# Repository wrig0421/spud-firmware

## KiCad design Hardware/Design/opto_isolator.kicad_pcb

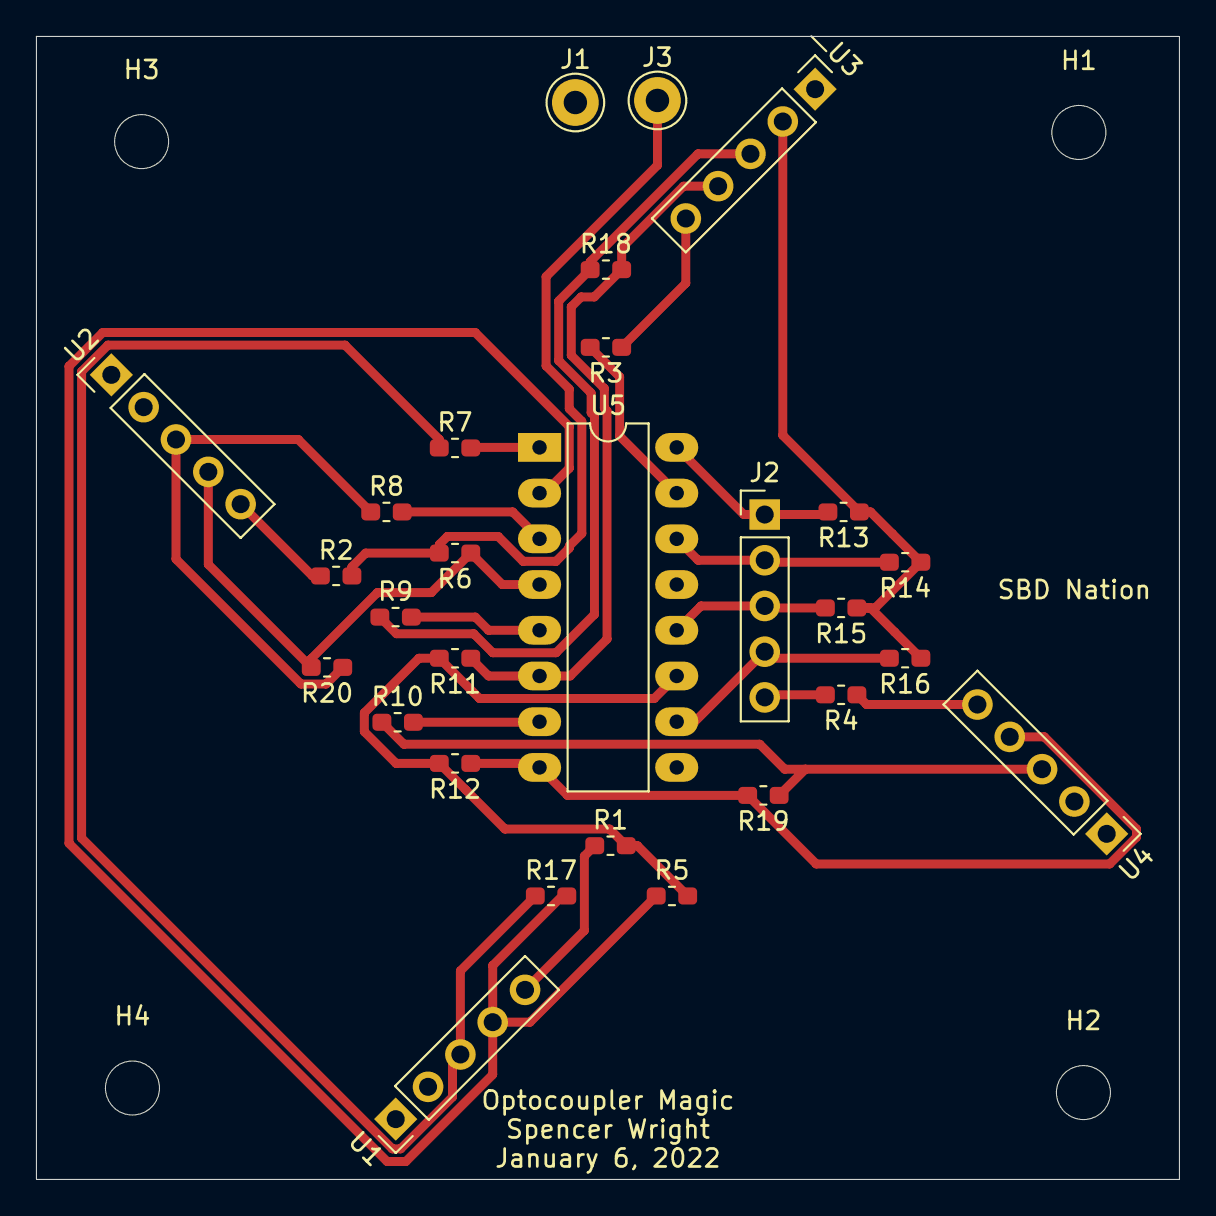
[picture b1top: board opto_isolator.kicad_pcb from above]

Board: 4 copper layers, 63.5 x 63.5 mm, 32 parts (0 on the bottom side), 22 nets.

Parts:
H1, H2, H3, H4: MountingHole; MountingHole_3mm
J1, J3: Conn_01x01_Male; Pin_D1.3mm_L11.0mm
J2: Conn_01x05_Male; PinHeader_1x05_P2.54mm_Vertical
R1, R2, R3, R4, R5, R6, R11, R12, R17, R18, R19, R20: DNI; R_0603_1608Metric_Pad1.05x0.95mm_HandSolder
R7, R8, R9, R10: 1k; R_0603_1608Metric_Pad1.05x0.95mm_HandSolder
R13, R14, R15, R16: 10k; R_0603_1608Metric_Pad1.05x0.95mm_HandSolder
U1, U2, U3, U4: receiver_433MHz; PinHeader_1x05_P2.54mm_Vertical
U5: PS2501-4; DIP-16_W7.62mm_LongPads

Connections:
/INT_0: J2.1, R13.2, U5.16
/INT_1: J2.2, R14.2, U5.14
/INT_2: J2.3, R15.2, U5.12
/INT_3: J2.4, R16.2, U5.10
/OUT_1_N: R5.1, R17.2, U1.4, U5.2
/OUT_1_P: R7.1, R17.1, U1.3
/OUT_2_N: R6.1, R20.2, U2.4, U5.4
/OUT_2_P: R8.1, R20.1, U2.3
/OUT_3_N: R11.1, R18.2, U3.4, U5.6
/OUT_3_P: R9.1, R18.1, U3.3
/OUT_4_N: R12.1, R19.2, U4.4, U5.8
/OUT_4_P: R10.1, R19.1, U4.3
GND: J2.5, J3.1, R1.2, R2.2, R3.2, R4.2, R5.2, R6.2, R11.2, R12.2, U1.1, U2.1, U3.1, U4.1, U5.9, U5.11, U5.13, U5.15
unnamed: R1.1, U1.5
unnamed: R2.1, U2.5
unnamed: R3.1, U3.5
unnamed: R4.1, U4.5
unnamed: R7.2, U5.1
unnamed: R8.2, U5.3
unnamed: R9.2, U5.5
unnamed: R10.2, U5.7
VCC: J1.1, R13.1, R14.1, R15.1, R16.1, U1.2, U2.2, U3.2, U4.2

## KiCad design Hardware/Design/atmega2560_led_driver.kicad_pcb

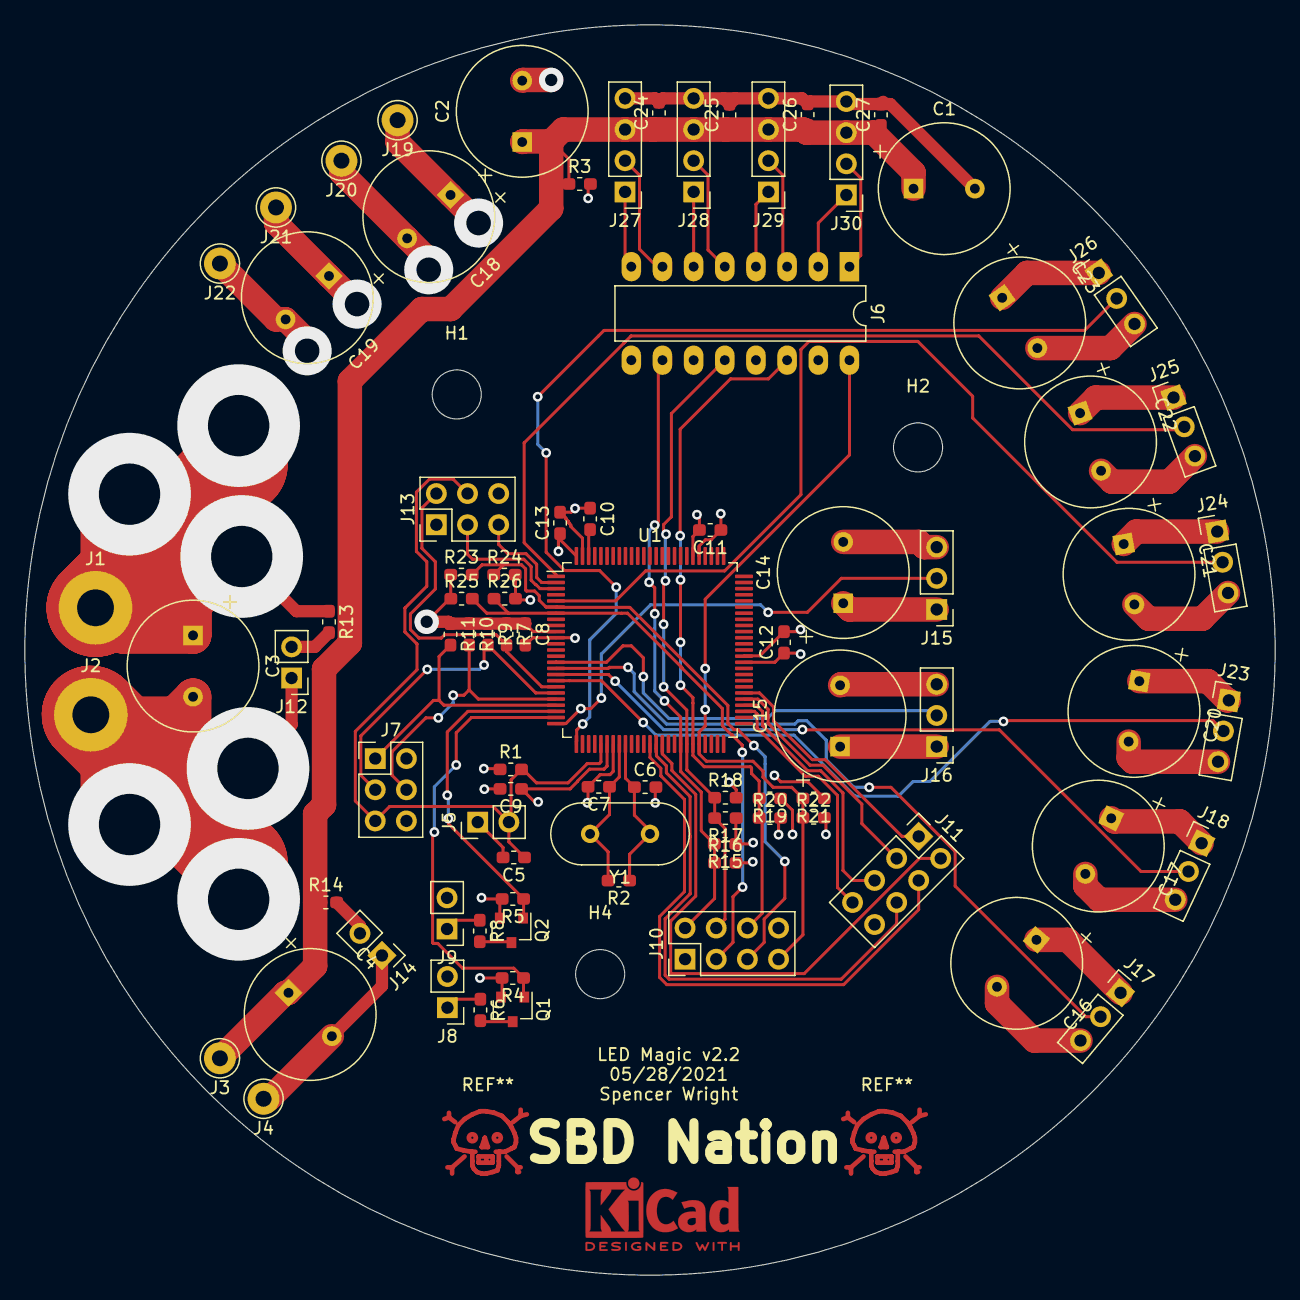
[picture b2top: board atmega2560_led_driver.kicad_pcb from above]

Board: 4 copper layers, 101.9 x 101.9 mm, 89 parts (0 on the bottom side), 50 nets.

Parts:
C1, C2, C3, C4, C14, C15, C16, C17, C18, C19, C20, C21, C22, C23: 10u; CP_Radial_Tantal_D10.5mm_P5.00mm
C5, C24, C25, C26, C27: 1u; R_0603_1608Metric_Pad1.05x0.95mm_HandSolder
C6, C7: CP1_Small; C_0603_1608Metric_Pad1.05x0.95mm_HandSolder
C8, C9, C10: 0.1u; R_0603_1608Metric_Pad1.05x0.95mm_HandSolder
C11, C12, C13: 0.1u; C_0603_1608Metric_Pad1.05x0.95mm_HandSolder
H1, H2, H4: MountingHole; MountingHole_4mm
J1, J2: Conn_01x01_Male; MountingHole_3mm_Pad
J3, J4, J19, J20, J21, J22: Conn_01x01_Male; Pin_D1.3mm_L11.0mm
J5, J8, J9, J12, J14: Conn_01x02_Male; PinHeader_1x02_P2.54mm_Vertical
J6: Conn_02x08_Counter_Clockwise; DIP-16_W7.62mm_LongPads
J7, J13: Conn_02x03_Odd_Even; PinHeader_2x03_P2.54mm_Vertical
J10, J11: Conn_02x04_Odd_Even; PinHeader_2x04_P2.54mm_Vertical
J15, J16, J17, J18, J23, J24, J25, J26: Conn_01x03_Male; PinHeader_1x03_P2.54mm_Vertical
J27, J28, J29, J30: Conn_01x04_Male; PinHeader_1x04_P2.54mm_Vertical
Q1, Q2: BSS138; SOT-23
R1, R7, R9, R10, R11, R15, R17, R19, R21, R23, R25: 10k; R_0603_1608Metric_Pad1.05x0.95mm_HandSolder
R2, R3, R4, R5: 1M; R_0603_1608Metric_Pad1.05x0.95mm_HandSolder
R6, R8: 100; R_0603_1608Metric_Pad1.05x0.95mm_HandSolder
R13: 1k; R_0603_1608Metric_Pad1.05x0.95mm_HandSolder
R14: 2.2k; R_0603_1608Metric_Pad1.05x0.95mm_HandSolder
R16, R18, R20, R22, R24, R26: DNI; R_0603_1608Metric_Pad1.05x0.95mm_HandSolder
U1: ATmega2560-16AU; TQFP-100_14x14mm_P0.5mm
Y1: 8M; Crystal_HC49-U_Vertical

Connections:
+5V: C3.1, C8.1, C9.1, C11.1, C12.1, C13.1, C14.1, C15.1, C16.1, C17.1, C18.1, C19.1, C20.1, C21.1, C22.1, C23.1, J1.1, J7.2, J8.2, J9.2, J10.1, J13.1, J15.1, J16.1, J17.1, J18.1, J19.1, J21.1, J23.1, J24.1, J25.1, J26.1, R1.1, R7.1, R9.1, R10.1, R11.1, R13.1, R15.1, R17.1, R19.1, R21.1, R23.1, R25.1, U1.10, U1.31, U1.61, U1.80, U1.100
+9V: C1.1, C2.1, C4.1, C24.1, C25.1, C26.1, C27.1, J3.1, J27.3, J28.3, J29.3, J30.3, R3.1, R14.1
/ATMEGA_D0_RX0: J13.5, U1.2
/ATMEGA_D1_TX0: J13.3, U1.3
/ATMEGA_D2_INT4: J10.5, R23.2, R24.1, U1.6
/ATMEGA_D3_INT5: J10.3, R25.2, R26.1, U1.7
/ATMEGA_D4_LED_OUT_7: J25.2, U1.1
/ATMEGA_D5_LED_OUT_6: J24.2, U1.5
/ATMEGA_D6_LED_OUT_2: J16.2, U1.15
/ATMEGA_D7_LED_OUT_3: J17.2, U1.16
/ATMEGA_D8_LED_OUT_4: J18.2, U1.17
/ATMEGA_D9_LED_OUT_5: J23.2, U1.18
/ATMEGA_D10_RED_LED: Q2.1, R5.1, U1.23
/ATMEGA_D11_GRN_LED: Q1.1, R4.1, U1.24
/ATMEGA_D12_LED_OUT_1: J15.2, U1.25
/ATMEGA_D13_LED_OUT_8: J26.2, U1.26
/ATMEGA_D18_INT3: J6.16, J10.7, R21.2, R22.1, U1.46
/ATMEGA_D19_INT2: J6.14, J10.6, R19.2, R20.1, U1.45
/ATMEGA_D20_INT1: J6.12, J10.4, R17.2, R18.1, U1.44
/ATMEGA_D21_INT0: J6.10, J10.2, R15.2, R16.1, U1.43
/ATMEGA_D34_GPIO: J11.1, U1.56
/ATMEGA_D35_GPIO: J11.3, U1.55
/ATMEGA_D36_GPIO: J11.5, U1.54
/ATMEGA_D37_GPIO: J11.7, U1.53
/ATMEGA_D44_GPIO: J11.2, U1.40
/ATMEGA_D45_GPIO: J11.6, U1.39
/ATMEGA_D46_GPIO: J11.4, U1.38
/ATMEGA_MISO: J7.1, R11.2, U1.22
/ATMEGA_MOSI: J7.4, R10.2, U1.21
/ATMEGA_NSS: J13.2, R7.2, U1.19
/ATMEGA_SCK: J7.3, R9.2, U1.20
/NRST: C5.1, J5.2, J7.5, J13.4, R1.2, U1.30
/OPTO_INT0_N: J6.8, J27.1
/OPTO_INT0_P: J6.7, J27.2
/OPTO_INT1_N: J6.6, J28.1
/OPTO_INT1_P: J6.5, J28.2
/OPTO_INT2_N: J6.4, J29.1
/OPTO_INT2_P: J6.3, J29.2
/OPTO_INT3_N: J6.2, J30.1
/OPTO_INT3_P: J6.1, J30.2
/XTAL1_HI: C6.1, R2.1, U1.34, Y1.1
/XTAL2_HI: C7.1, R2.2, U1.33, Y1.2
GND: C1.2, C2.2, C3.2, C4.2, C5.2, C6.2, C7.2, C8.2, C9.2, C10.1, C11.2, C12.2, C13.2, C14.2, C15.2, C16.2, C17.2, C18.2, C19.2, C20.2, C21.2, C22.2, C23.2, C24.2, C25.2, C26.2, C27.2, J2.1, J4.1, J5.1, J6.9, J6.11, J6.13, J6.15, J7.6, J10.8, J11.8, J12.1, J13.6, J14.1, J15.3, J16.3, J17.3, J18.3, J20.1, J22.1, J23.3, J24.3, J25.3, J26.3, J27.4, J28.4, J29.4, J30.4, Q1.2, Q2.2, R3.2, R4.2, R5.2, R16.2, R18.2, R20.2, R22.2, R24.2, R26.2, U1.11, U1.32, U1.62, U1.81, U1.99
unnamed: C10.2, U1.98
unnamed: J8.1, R6.1
unnamed: J9.1, R8.1
unnamed: J12.2, R13.2
unnamed: J14.2, R14.2
unnamed: Q1.3, R6.2
unnamed: Q2.3, R8.2

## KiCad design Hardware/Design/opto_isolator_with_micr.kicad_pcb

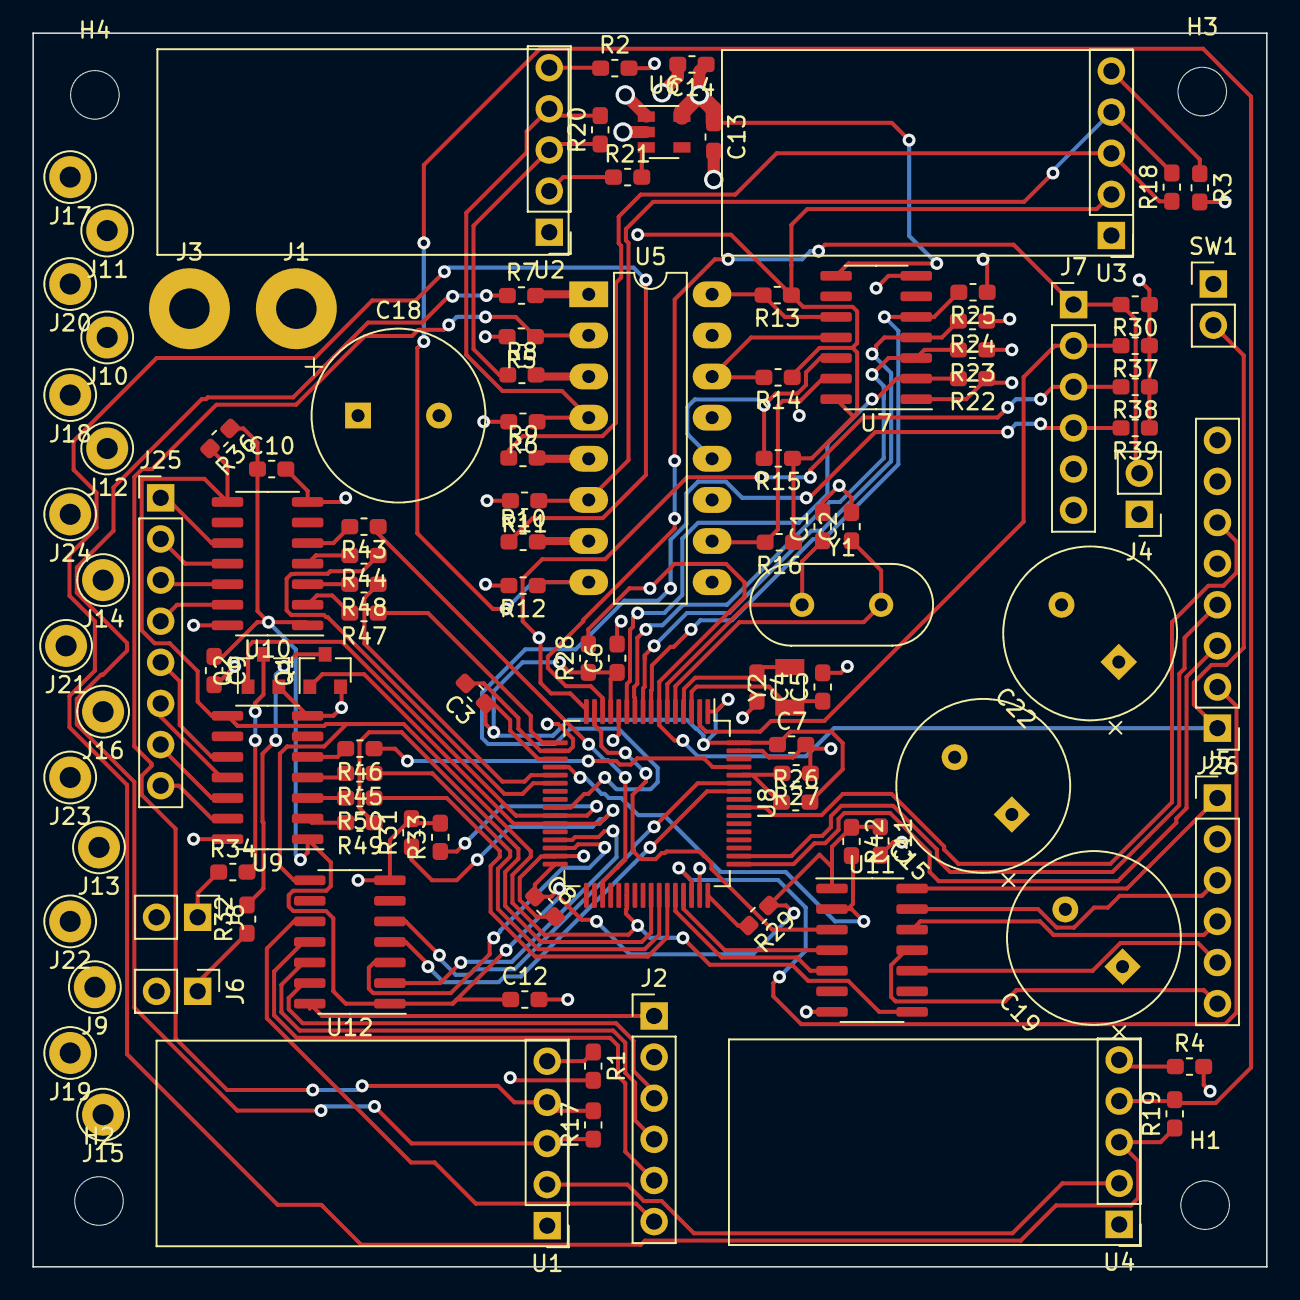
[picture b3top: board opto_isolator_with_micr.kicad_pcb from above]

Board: 4 copper layers, 76.2 x 76.2 mm, 112 parts (0 on the bottom side), 92 nets.

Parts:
C1, C2, C4, C5: CP1_Small; C_0603_1608Metric_Pad1.05x0.95mm_HandSolder
C3, C9, C10, C11, C12, C13: 1u; C_0603_1608Metric_Pad1.05x0.95mm_HandSolder
C6: 0.1u; C_0603_1608Metric_Pad1.05x0.95mm_HandSolder
C7: 0.01u; C_0603_1608Metric_Pad1.05x0.95mm_HandSolder
C8, C14: 10u; C_0603_1608Metric_Pad1.05x0.95mm_HandSolder
C15, C18, C19, C22: DNI; CP_Radial_Tantal_D10.5mm_P5.00mm
H1, H2, H3, H4: MountingHole; MountingHole_3mm
J1, J3: Conn_01x01_Male; MountingHole_2.5mm_Pad
J2, J5, J7: Conn_01x06_Male; PinHeader_1x06_P2.54mm_Vertical
J4, J6, J8: Conn_01x02_Male; PinHeader_1x02_P2.54mm_Vertical
J9, J10, J11, J12, J13, J14, J15, J16, J17, J18, J19, J20, J21, J22, J23, J24: Conn_01x01_Male; Pin_D1.3mm_L11.0mm
J25, J26: Conn_01x08_Male; PinHeader_1x08_P2.54mm_Vertical
Q1, Q2: BSS138; SOT-23
R1, R2, R3, R4, R5, R6, R11, R12, R18, R22, R23, R24, R25, R26: DNI; R_0603_1608Metric_Pad1.05x0.95mm_HandSolder
R7, R8, R9, R10, R30, R32, R34, R43, R44, R45, R46, R47, R48, R49, R50: 1k; R_0603_1608Metric_Pad1.05x0.95mm_HandSolder
R13, R14, R15, R16, R17, R19, R20, R21, R27, R37, R38, R39: 10k; R_0603_1608Metric_Pad1.05x0.95mm_HandSolder
R28, R31, R33, R36, R42: 100k; R_0603_1608Metric_Pad1.05x0.95mm_HandSolder
R29: 0; R_0603_1608Metric_Pad1.05x0.95mm_HandSolder
SW1: SW_Push; PinHeader_1x02_P2.54mm_Vertical
U1, U2, U3, U4: receiver_433MHz; PinHeader_1x05_P2.54mm_Vertical
U5: PS2501-4; DIP-16_W7.62mm_LongPads
U6: LD39015M18R; SOT-23-5
U7, U9, U10, U11, U12: TXB0104D; SOIC-14_3.9x8.7mm_P1.27mm
U8: STM32L431RCTx; LQFP-64_10x10mm_P0.5mm
Y1: Crystal; Crystal_HC49-U_Vertical
Y2: Crystal; Crystal_SMD_3215-2Pin_3.2x1.5mm

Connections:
+1V8: C3.1, C6.1, C7.1, C8.1, C9.1, C10.1, C11.1, C12.1, C13.1, C14.1, J7.5, J26.7, R22.1, R23.1, R24.1, R25.1, R26.2, R28.1, R29.1, R30.1, R36.1, R37.1, R38.1, R39.1, R42.1, U6.5, U7.1, U7.8, U8.1, U8.13, U8.19, U8.32, U8.64, U9.1, U10.1, U11.1, U12.1
+5V: C15.1, C18.1, C19.1, C22.1, J1.1, J6.2, J8.2, J9.1, J10.1, J11.1, J12.1, J13.1, J14.1, J15.1, J16.1, R13.1, R14.1, R15.1, R16.1, R21.1, U1.2, U2.2, U3.2, U4.2, U6.1, U7.14, U9.14, U10.14
/INT_0: R13.2, U5.16, U7.10
/INT_1: R14.2, U5.14, U7.11
/INT_2: R15.2, U5.12, U7.12
/INT_3: R16.2, U5.10, U7.13
/OUT_1_N: R5.1, R17.2, U1.4, U5.2
/OUT_1_P: R7.1, R17.1, U1.3
/OUT_2_N: R6.1, R20.2, U2.4, U5.4
/OUT_2_P: R8.1, R20.1, U2.3
/OUT_3_N: R11.1, R18.2, U3.4, U5.6
/OUT_3_P: R9.1, R18.1, U3.3
/OUT_4_N: R12.1, R19.2, U4.4, U5.8
/OUT_4_P: R10.1, R19.1, U4.3
/Sheet6227BA78/I2C2_SCL: U8.29, U12.2
/Sheet6227BA78/I2C2_SCL_SHIFTED: J2.3, U12.13
/Sheet6227BA78/I2C2_SDA: U8.30, U12.3
/Sheet6227BA78/I2C2_SDA_SHIFTED: J2.4, U12.12
/Sheet6227BA78/I2C_UART_VREF: J2.1, U12.14
/Sheet6227BA78/LED_GREEN: Q1.1, R31.1, U8.27
/Sheet6227BA78/LED_RED: Q2.1, R33.1, U8.26
/Sheet6227BA78/LED_STRIP_OUT_1: R47.2, U10.2
/Sheet6227BA78/LED_STRIP_OUT_1_SHIFTED: J25.4, U10.13
/Sheet6227BA78/LED_STRIP_OUT_2: R48.2, U10.3
/Sheet6227BA78/LED_STRIP_OUT_2_SHIFTED: J25.3, U10.12
/Sheet6227BA78/LED_STRIP_OUT_3: R44.2, U10.4
/Sheet6227BA78/LED_STRIP_OUT_3_SHIFTED: J25.2, U10.11
/Sheet6227BA78/LED_STRIP_OUT_4: R43.2, U10.5
/Sheet6227BA78/LED_STRIP_OUT_4_SHIFTED: J25.1, U10.10
/Sheet6227BA78/LED_STRIP_OUT_5: R49.2, U9.2
/Sheet6227BA78/LED_STRIP_OUT_5_SHIFTED: J25.8, U9.13
/Sheet6227BA78/LED_STRIP_OUT_6: R50.2, U9.3
/Sheet6227BA78/LED_STRIP_OUT_6_SHIFTED: J25.7, U9.12
/Sheet6227BA78/LED_STRIP_OUT_7: R45.2, U9.4
/Sheet6227BA78/LED_STRIP_OUT_7_SHIFTED: J25.6, U9.11
/Sheet6227BA78/LED_STRIP_OUT_8: R46.2, U9.5
/Sheet6227BA78/LED_STRIP_OUT_8_SHIFTED: J25.5, U9.10
/Sheet6227BA78/LVL_SHIFTER_EN: R36.2, U8.38, U9.8, U10.8, U11.8, U12.8
/Sheet6227BA78/NJTRST: J26.6, U8.56
/Sheet6227BA78/NRST: J26.1, R28.2, SW1.2, U8.7
/Sheet6227BA78/SPI1_CSN: R42.2, U8.20, U11.2
/Sheet6227BA78/SPI1_CSN_SHIFTED: J5.3, U11.13
/Sheet6227BA78/SPI1_MISO: U8.44, U11.5
/Sheet6227BA78/SPI1_MISO_SHIFTED: J5.5, U11.10
/Sheet6227BA78/SPI1_MOSI: U8.45, U11.4
/Sheet6227BA78/SPI1_MOSI_SHIFTED: J5.6, U11.11
/Sheet6227BA78/SPI1_SCK: U8.15, U11.3
/Sheet6227BA78/SPI1_SCK_SHIFTED: J5.4, U11.12
/Sheet6227BA78/SPI_VREF: J5.1, U11.14
/Sheet6227BA78/SWCLK: J26.3, U8.49
/Sheet6227BA78/SWDIO: J26.2, U8.46
/Sheet6227BA78/TDI: J26.4, U8.50
/Sheet6227BA78/USART1_RX: U8.59, U12.5
/Sheet6227BA78/USART1_RX_SHIFTED: J2.6, U12.10
/Sheet6227BA78/USART1_TX: U8.58, U12.4
/Sheet6227BA78/USART1_TX_SHIFTED: J2.5, U12.11
/Sheet6227BA78/WKUP1: J4.2, J7.1, R30.2, U8.14
/Sheet6227BA78/WKUP2: J7.2, R37.2, U8.2
/Sheet6227BA78/WKUP4: J7.3, R38.2, U8.16
/Sheet6227BA78/WKUP5: J7.4, R39.2, U8.25
/Sheet6227BA78/XTAL1: C4.1, U8.4, Y2.1
/Sheet6227BA78/XTAL1_HI: C1.1, U8.6, Y1.1
/Sheet6227BA78/XTAL2: C5.1, U8.3, Y2.2
/Sheet6227BA78/XTAL2_HI: C2.1, U8.5, Y1.2
GND: C1.2, C2.2, C3.2, C4.2, C5.2, C6.2, C7.2, C8.2, C9.2, C10.2, C11.2, C12.2, C13.2, C14.2, C15.2, C18.2, C19.2, C22.2, J2.2, J3.1, J4.1, J5.2, J7.6, J17.1, J18.1, J19.1, J20.1, J21.1, J22.1, J23.1, J24.1, J26.8, Q1.2, Q2.2, R1.2, R2.2, R3.2, R4.2, R5.2, R6.2, R11.2, R12.2, R27.1, R31.2, R33.2, SW1.1, U1.1, U2.1, U3.1, U4.1, U5.9, U5.11, U5.13, U5.15, U6.2, U7.7, U8.12, U8.18, U8.31, U8.47, U8.63, U9.7, U10.7, U11.7, U12.7
INT_0_SHIFTED: R25.2, U7.5, U8.8
INT_1_SHIFTED: R24.2, U7.4, U8.9
INT_2_SHIFTED: R23.2, U7.3, U8.10
INT_3_SHIFTED: R22.2, U7.2, U8.11
unnamed: J6.1, R32.1
unnamed: J8.1, R34.1
unnamed: Q1.3, R32.2
unnamed: Q2.3, R34.2
unnamed: R1.1, U1.5
unnamed: R2.1, U2.5
unnamed: R3.1, U3.5
unnamed: R4.1, U4.5
unnamed: R7.2, U5.1
unnamed: R8.2, U5.3
unnamed: R9.2, U5.5
unnamed: R10.2, U5.7
unnamed: R21.2, U6.3
unnamed: R26.1, R27.2, U8.60
unnamed: R29.2, U8.48
unnamed: R43.1, U8.35
unnamed: R44.1, U8.22
unnamed: R45.1, U8.42
unnamed: R46.1, U8.61
unnamed: R47.1, U8.17
unnamed: R48.1, U8.21
unnamed: R49.1, U8.41
unnamed: R50.1, U8.43

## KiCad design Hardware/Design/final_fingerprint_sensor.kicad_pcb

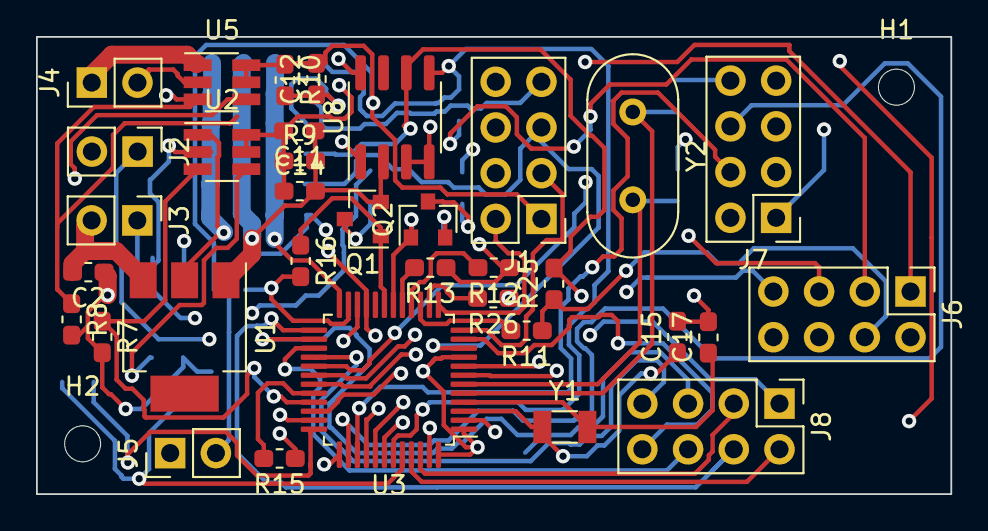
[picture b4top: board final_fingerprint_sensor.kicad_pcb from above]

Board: 4 copper layers, 50.8 x 25.4 mm, 59 parts (0 on the bottom side), 52 nets.

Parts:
C1, C4, C6, C7, C8, C13, C14: 1u; C_0603_1608Metric_Pad1.05x0.95mm_HandSolder
C2, C3, C11, C12: 10u; C_0603_1608Metric_Pad1.05x0.95mm_HandSolder
C5, C15, C16, C17: CP1_Small; C_0603_1608Metric_Pad1.05x0.95mm_HandSolder
C9, C10: 220p; C_0603_1608Metric_Pad1.05x0.95mm_HandSolder
H1, H2: MountingHole_Pad; MountingHole_2mm
J1, J6, J7, J8: Conn_01x08_Male; PinHeader_2x04_P2.54mm_Vertical
J2, J3, J4, J5: Conn_01x02_Male; PinHeader_1x02_P2.54mm_Vertical
Q1, Q2: BSS138; SOT-23
R1, R7, R8, R16, R18: 1M; R_0603_1608Metric_Pad1.05x0.95mm_HandSolder
R2, R3: 10k; C_0603_1608Metric_Pad1.05x0.95mm_HandSolder
R4, R9, R10, R12, R14, R15, R25: DNI; R_0603_1608Metric_Pad1.05x0.95mm_HandSolder
R5, R6, R20, R23: 10k; R_0603_1608Metric_Pad1.05x0.95mm_HandSolder
R11, R13, R26: 0; R_0603_1608Metric_Pad1.05x0.95mm_HandSolder
R17, R19: 100; R_0603_1608Metric_Pad1.05x0.95mm_HandSolder
U1: TLV1117-33; SOT-223
U2, U5: TPS22918; SOT-23-6_Handsoldering
U3: STM32L433CCTx; LQFP-48_7x7mm_P0.5mm
U8: CAT24C256; SOIC-8_3.9x4.9mm_P1.27mm
Y1: 32.768k Crystal; Crystal_SMD_3215-2Pin_3.2x1.5mm
Y2: 8M; Crystal_HC49-U_Vertical

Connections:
+3V3: C3.2, C4.2, C6.1, C7.1, C8.2, C13.1, J7.1, R1.1, R2.1, R3.1, R4.1, R5.1, R6.1, R23.1, U1.2, U2.1, U3.1, U3.9, U3.24, U3.36, U3.48, U8.1, U8.8
+5V: C2.2, J2.2, J3.2, J4.1, U1.3, U5.1
/DISP_BUSY: J6.8, U3.31
/DISP_CSN_BACKUP: R15.2, U3.32
/DISP_DATA_CMD_CTRL: J6.6, U3.29
/DISP_PWR_ON: R7.1, U2.3, U3.33
/DISP_RESET_N: J6.7, U3.30
/DISP_VCC: C11.2, C14.1, J6.1, R9.1, U2.5, U2.6
/FINGER_IO: J7.7, U3.22
/FINGER_PWR_ON: R8.1, U3.21, U5.3
/FINGER_VCC: C1.1, C12.2, J1.1, R10.1, U5.5, U5.6
/GRN_LED: Q1.1, R16.1, U3.19
/I2C1_SCL: R5.2, R25.2, U3.42, U8.6
/I2C1_SDA: R6.2, R14.2, U3.43, U8.5
/INT1: J1.7, R3.2, U3.2
/INT2: J1.5, R2.2, U3.10
/KEYPAD_C1: J8.5, U3.26
/KEYPAD_C2: J8.6, U3.27
/KEYPAD_C3: J8.7, U3.28
/KEYPAD_C4: J8.8, U3.11
/KEYPAD_R1: J8.1, U3.41
/KEYPAD_R2: J8.2, U3.45
/KEYPAD_R3: J8.3, U3.46
/KEYPAD_R4: J8.4, U3.25
/NJTRST: J7.5, U3.40
/RED_LED: Q2.1, R18.1, U3.18
/RST: J5.2, R23.2, U3.7
/SPI1_MISO: R12.2, U3.16
/SPI1_MOSI: R13.2, U3.17
/SPI1_NSS: R26.2, U3.14
/SPI1_SCK: R11.2, U3.15
/SWCLK: J7.3, U3.37
/SWDIO: J7.2, U3.34
/SWO: J7.4, U3.39
/TDI: J7.6, U3.38
/USART2_RX_FROM_STM: J1.2, U3.13
/USART2_TX_FROM_STM: J1.3, U3.12
/XTAL1: C15.1, U3.3, Y1.2
/XTAL1_HI: C5.1, U3.5, Y2.1
/XTAL2: C17.1, U3.4, Y1.1
/XTAL2_HI: C16.1, U3.6, Y2.2
GND: C1.2, C2.1, C3.1, C4.1, C5.2, C6.2, C7.2, C8.1, C9.2, C10.2, C11.1, C12.1, C13.2, C14.2, C15.2, C16.2, C17.2, J1.4, J1.6, J1.8, J4.2, J5.1, J6.2, J7.8, Q1.2, Q2.2, R1.2, R7.2, R8.2, R9.2, R10.2, R16.2, R18.2, R20.2, U1.1, U2.2, U3.8, U3.23, U3.35, U3.47, U5.2, U8.2, U8.3, U8.4
unnamed: C9.1, U2.4
unnamed: C10.1, U5.4
unnamed: J2.1, R17.1
unnamed: J3.1, R19.1
unnamed: J6.3, R12.1, R13.1, R14.1
unnamed: J6.4, R11.1, R25.1
unnamed: J6.5, R15.1, R26.1
unnamed: Q1.3, R17.2
unnamed: Q2.3, R19.2
unnamed: R4.2, R20.1, U3.44

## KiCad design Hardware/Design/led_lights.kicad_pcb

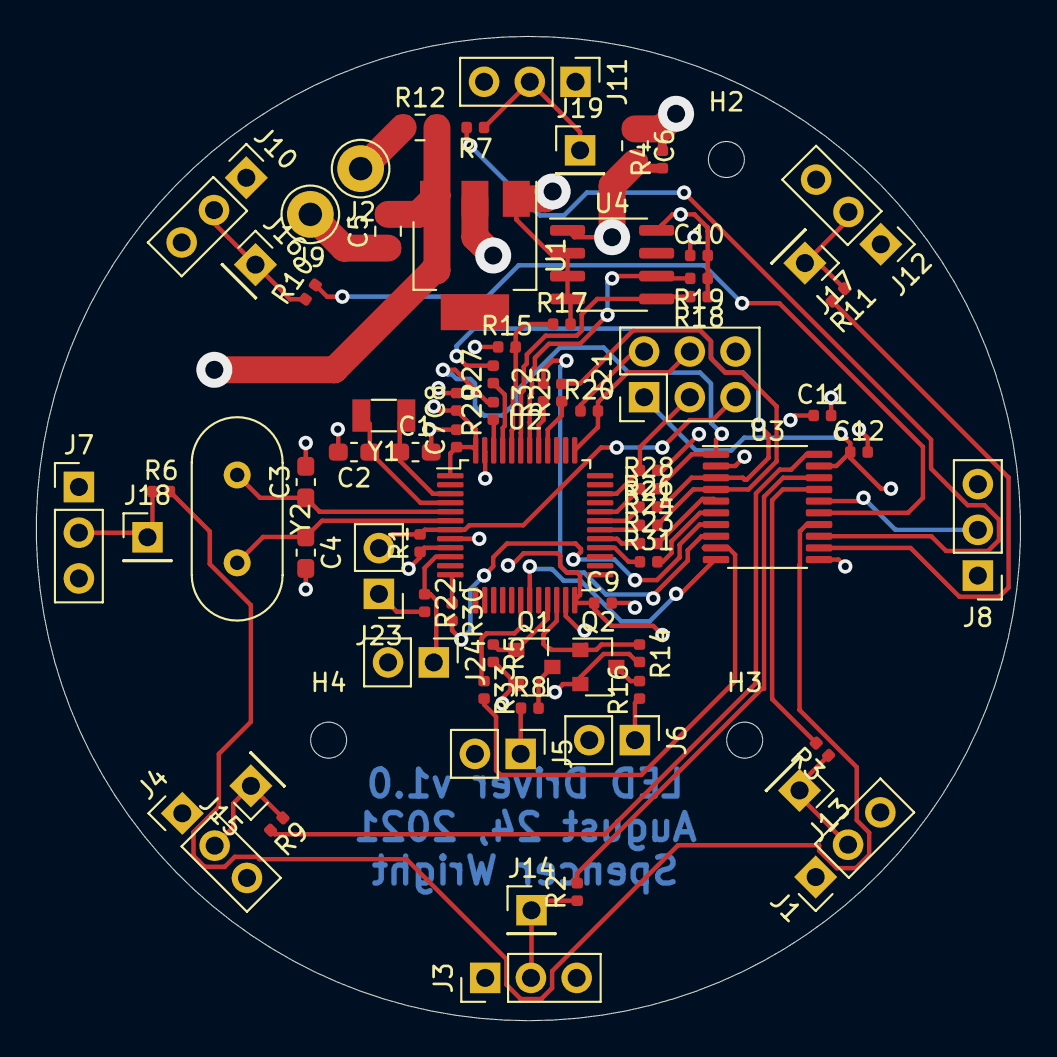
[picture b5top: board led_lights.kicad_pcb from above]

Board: 4 copper layers, 54.7 x 54.7 mm, 77 parts (0 on the bottom side), 56 nets.

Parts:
C1, C2, C3, C4: CP1_Small; C_0603_1608Metric_Pad1.05x0.95mm_HandSolder
C5, C6: 10u; C_0805_2012Metric
C7, C8, C9, C10, C11, C12: 1u; C_0402_1005Metric
H2, H3, H4: MountingHole_Pad; MountingHole_2mm
J1, J3, J4, J7, J8, J10, J11, J12: Conn_01x03_Male; PinHeader_1x03_P2.54mm_Vertical
J2, J9: Conn_01x01_Male; Pin_D1.3mm_L11.0mm
J5, J6, J23, J24: Conn_01x02_Male; PinHeader_1x02_P2.54mm_Vertical
J13, J14, J15, J16, J17, J18, J19: Conn_01x01_Male; PinHeader_1x01_P2.54mm_Vertical
J21: Conn_01x06_Male; PinHeader_2x03_P2.54mm_Vertical
Q1, Q2: BSS138; SOT-23
R1, R15, R18, R19, R20, R21, R22: 10k; R_0402_1005Metric
R2, R3, R6, R7, R9, R10, R11, R17, R24, R26, R28: DNI; R_0402_1005Metric
R4, R5, R14: 1M; R_0402_1005Metric
R8, R16: 100; R_0402_1005Metric
R12: DNI; R_0805_2012Metric
R23, R25, R27, R29, R30, R31, R32, R33: 0; R_0402_1005Metric
U1: TLV1117-33; SOT-223
U2: STM32F030C8Tx; LQFP-48_7x7mm_P0.5mm
U3: TXS0108EPW; TSSOP-20_4.4x6.5mm_P0.65mm
U4: CAT24C256; SOIC-8_3.9x4.9mm_P1.27mm
Y1: 32.768k Crystal; Crystal_SMD_3215-2Pin_3.2x1.5mm
Y2: 8M; Crystal_HC49-U_Vertical

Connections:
/GRN_LED: Q1.1, R5.1, U2.21
/LED_STRIP_OUT_0: J8.2, U3.16
/LED_STRIP_OUT_1: R3.2, U3.17
/LED_STRIP_OUT_2: R2.2, U3.18
/LED_STRIP_OUT_3: R9.2, U3.20
/LED_STRIP_OUT_4: R6.2, U3.14
/LED_STRIP_OUT_5: R10.2, U3.15
/LED_STRIP_OUT_6: R7.2, U3.13
/LED_STRIP_OUT_7: R11.2, U3.12
/LVL_SHIFTER_EN: U2.19, U3.10
/NRST: J21.5, J23.2, R1.2, U2.7
/RED_LED: Q2.1, R14.1, U2.22
/ST_LED_OUT_0: R23.2, U3.5
/ST_LED_OUT_1: R24.2, R25.2, U3.4
/ST_LED_OUT_2: R26.2, R27.2, U3.3
/ST_LED_OUT_3: R28.2, R29.2, U3.1
/ST_LED_OUT_4: R30.2, U3.7
/ST_LED_OUT_5: R31.2, U3.6
/ST_LED_OUT_6: R32.2, U3.8
/ST_LED_OUT_7: R33.2, U3.9
/ST_SCL: R19.2, U2.42, U4.6
/ST_SDA: R18.2, U2.43, U4.5
/ST_SWCLK: J21.4, R20.2, U2.37
/ST_SWDIO: J21.3, R21.2, U2.34
/ST_TIM1_CH1: R23.1, U2.29
/ST_TIM1_CH2: R24.1, U2.30
/ST_TIM1_CH3: R26.1, U2.31
/ST_TIM1_CH4: R28.1, U2.32
/ST_TIM3_CH1: R25.1, U2.40
/ST_TIM3_CH2: R32.1, U2.41
/ST_TIM3_CH3: R33.1, U2.18
/ST_TIM15_CH1: R30.1, U2.12
/ST_TIM15_CH2: R31.1, U2.28
/ST_TIM16_CH1: R27.1, U2.45
/ST_TIM17_CH1: R29.1, U2.46
/SYS_5V: C5.2, C12.1, J1.1, J3.1, J4.1, J5.2, J6.2, J7.1, J8.1, J10.1, J11.1, J12.1, J21.1, R12.2, U1.3, U3.19
/VIN: J2.1, R12.1
/XTAL1: C1.1, U2.3, Y1.2
/XTAL1_HI: C3.1, U2.5, Y2.1
/XTAL2: C2.1, U2.4, Y1.1
/XTAL2_HI: C4.1, U2.6, Y2.2
GND: C1.2, C2.2, C3.2, C4.2, C5.1, C6.1, C7.2, C8.2, C9.2, C10.1, C11.2, C12.2, J1.3, J3.3, J4.3, J7.3, J8.3, J9.1, J10.3, J11.3, J12.3, J21.6, J23.1, Q1.2, Q2.2, R4.2, R5.2, R14.2, R17.2, R22.2, U1.1, U2.8, U2.23, U2.47, U3.11, U4.2, U4.3, U4.4
unnamed: J1.2, J13.1, R3.1
unnamed: J5.1, R8.1
unnamed: J6.1, R16.1
unnamed: J10.2, J16.1, R10.1
unnamed: J11.2, J19.1, R7.1
unnamed: J12.2, J17.1, R11.1
unnamed: J3.2, J14.1, R2.1
unnamed: J4.2, J15.1, R9.1
unnamed: J7.2, J18.1, R6.1
unnamed: J24.1, R22.1, U2.10
unnamed: Q1.3, R8.2
unnamed: Q2.3, R16.2
unnamed: R15.2, R17.1, U2.44
VCC: C6.2, C7.1, C8.1, C9.1, C10.2, C11.1, J21.2, J24.2, R1.1, R4.1, R15.1, R18.1, R19.1, R20.1, R21.1, U1.2, U2.1, U2.9, U2.24, U2.48, U3.2, U4.1, U4.8

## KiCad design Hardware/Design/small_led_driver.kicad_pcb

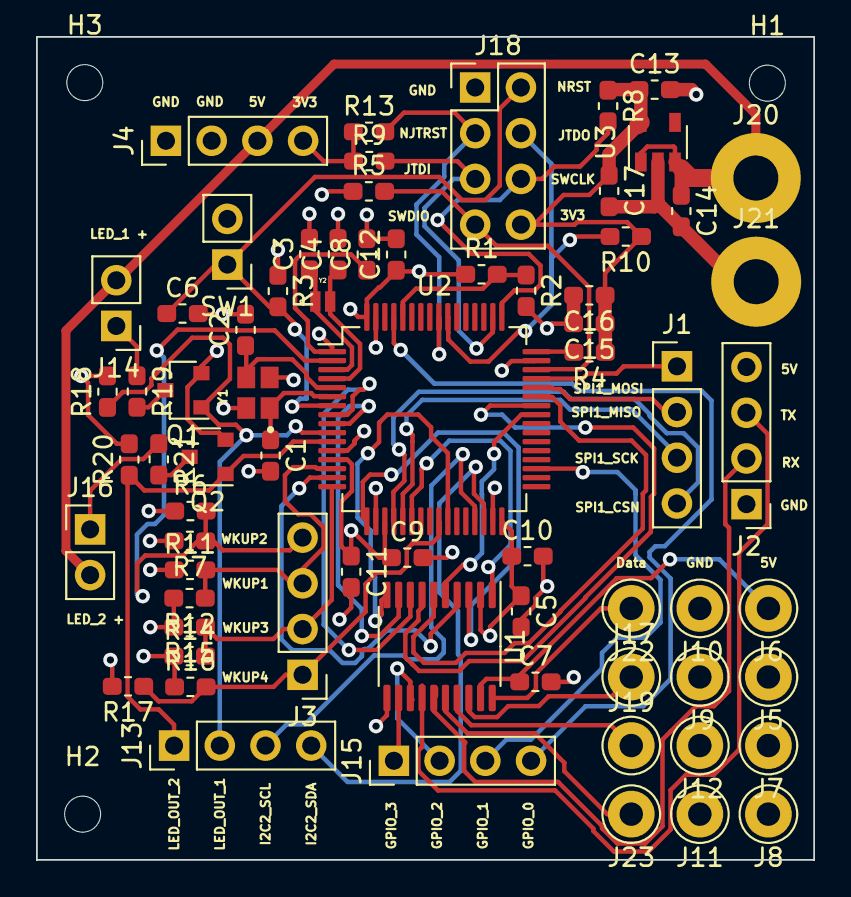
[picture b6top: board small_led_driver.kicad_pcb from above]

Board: 4 copper layers, 43.2 x 45.7 mm, 72 parts (0 on the bottom side), 50 nets.

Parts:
C1, C2: 6p; C_0603_1608Metric_Pad1.05x0.95mm_HandSolder
C3, C4: 8p; C_0603_1608Metric_Pad1.05x0.95mm_HandSolder
C5, C6, C7, C8, C9, C10, C11, C12: 0.1u; C_0603_1608Metric_Pad1.05x0.95mm_HandSolder
C13: 4.7u; C_0603_1608Metric_Pad1.05x0.95mm_HandSolder
C14, C17: 1u; C_0603_1608Metric_Pad1.05x0.95mm_HandSolder
C15: 0.01u; C_0603_1608Metric_Pad1.05x0.95mm_HandSolder
C16: 1; C_0603_1608Metric_Pad1.05x0.95mm_HandSolder
H1, H2, H3: MountingHole; MountingHole_2mm
J1, J2, J3, J4, J13, J15: Conn_01x04_Male; PinHeader_1x04_P2.54mm_Vertical
J5, J6, J7, J8, J9, J10, J11, J12, J17, J19, J22, J23: Conn_01x01_Male; Pin_D1.3mm_L11.0mm
J14, J16: Conn_01x02_Male; PinHeader_1x02_P2.54mm_Vertical
J18: Conn_01x08_Male; PinHeader_2x04_P2.54mm_Vertical
J20, J21: Conn_01x01_Male; MountingHole_2.5mm_Pad
Q1, Q2: BSS138; SOT-23
R1, R3, R5, R6, R8, R9, R10, R11, R13, R14, R16: 10k; R_0603_1608Metric_Pad1.05x0.95mm_HandSolder
R2, R7, R12, R15, R17: DNI; R_0603_1608Metric_Pad1.05x0.95mm_HandSolder
R4: 0; R_0603_1608Metric_Pad1.05x0.95mm_HandSolder
R18, R20: 100k; R_0603_1608Metric_Pad1.05x0.95mm_HandSolder
R19, R21: 1k; R_0603_1608Metric_Pad1.05x0.95mm_HandSolder
SW1: SW_DIP_x01; PinHeader_1x02_P2.54mm_Vertical
U1: TXS0108EPW; TSSOP-20_4.4x6.5mm_P0.65mm
U2: STM32L431RCTx; LQFP-64_10x10mm_P0.5mm
U3: LP5907MFX-3.3; SOT-23-5
Y1: ECS-480-8-36-RWN-TR; XTAL_ECS-480-8-36-RWN-TR
Y2: ECS-.327-9-1210-TR; XTAL_ECS-.327-9-1210-TR

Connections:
+3V3: C5.1, C8.1, C9.1, C10.1, C11.1, C12.1, C13.1, C15.1, C16.1, C17.1, J4.4, J18.8, R1.1, R3.1, R4.1, R5.1, R6.1, R8.1, R9.1, R10.1, R11.1, R13.1, R14.1, R16.1, U1.2, U2.1, U2.13, U2.19, U2.32, U2.64, U3.5
+5V: C7.1, C14.1, J2.4, J4.3, J5.1, J6.1, J7.1, J8.1, J14.2, J16.2, J20.1, U1.19, U3.1, U3.3
/BOOT0: R1.2, R2.1, U2.60
/GPIO_0: J15.4, U2.61
/GPIO_1: J15.3, U2.35
/GPIO_2: U1.8, U2.8
/GPIO_2_SHIFT: J15.2, U1.13
/GPIO_3: U1.9, U2.9
/GPIO_3_SHIFT: J15.1, U1.12
/I2C2_SCL: J13.3, U2.29
/I2C2_SDA: J13.4, U2.30
/JTDI: J18.5, R9.2, U2.50
/JTDO: J18.4, R10.2, U2.55
/LED_OUT_1: J13.2, Q1.1, R18.1, U2.10
/LED_OUT_2: J13.1, Q2.1, R20.1, U2.11
/LEVEL_SHIFTER_EN: U1.10, U2.26
/NJTRST: J18.3, R13.2, U2.56
/NRST: C6.1, J18.2, R3.2, SW1.1, U2.7
/OSC48_HI: C2.1, U2.5, Y1.3
/OSC48_LO: C1.1, U2.6, Y1.1
/SPI1_CSN: J1.4, U2.20
/SPI1_MISO: J1.2, U2.44
/SPI1_MOSI: J1.1, U2.45
/SPI1_SCK: J1.3, U2.21
/SWCLK: J18.6, R8.2, U2.49
/SWDIO: J18.7, R5.2, U2.46
/TIM1_CH1: U1.5, U2.41
/TIM1_CH1_SHIFT: J23.1, U1.16
/TIM2_CH2: U1.4, U2.15
/TIM2_CH2_SHIFT: J19.1, U1.17
/TIM15_CH1: U1.3, U2.17
/TIM15_CH1_SHIFT: J17.1, U1.18
/TIM16_CH1: U1.1, U2.22
/TIM16_CH1_SHIFT: J22.1, U1.20
/USART1_RX: U1.6, U2.43
/USART1_RX_SHIFT: J2.2, U1.15
/USART1_TX: U1.7, U2.42
/USART1_TX_SHIFT: J2.3, U1.14
/WKUP1: J3.3, R11.2, R12.1, U2.14
/WKUP2: J3.4, R6.2, R7.1, U2.2
/WKUP3: J3.1, R16.2, R17.1, U2.25
/WKUP4: J3.2, R14.2, R15.1, U2.16
GND1: C1.2, C2.2, C3.2, C4.2, C5.2, C6.2, C7.2, C8.2, C9.2, C10.2, C11.2, C12.2, C13.2, C14.2, C15.2, C16.2, C17.2, J2.1, J4.1, J4.2, J9.1, J10.1, J11.1, J12.1, J18.1, J21.1, Q1.2, Q2.2, R2.2, R7.2, R12.2, R15.2, R17.2, R18.2, R20.2, SW1.2, U1.11, U2.12, U2.18, U2.31, U2.47, U2.63, U3.2, Y1.2, Y1.4
unnamed: C3.1, U2.3, Y2.1
unnamed: C4.1, U2.4, Y2.2
unnamed: J14.1, R19.1
unnamed: J16.1, R21.1
unnamed: Q1.3, R19.2
unnamed: Q2.3, R21.2
unnamed: R4.2, U2.48

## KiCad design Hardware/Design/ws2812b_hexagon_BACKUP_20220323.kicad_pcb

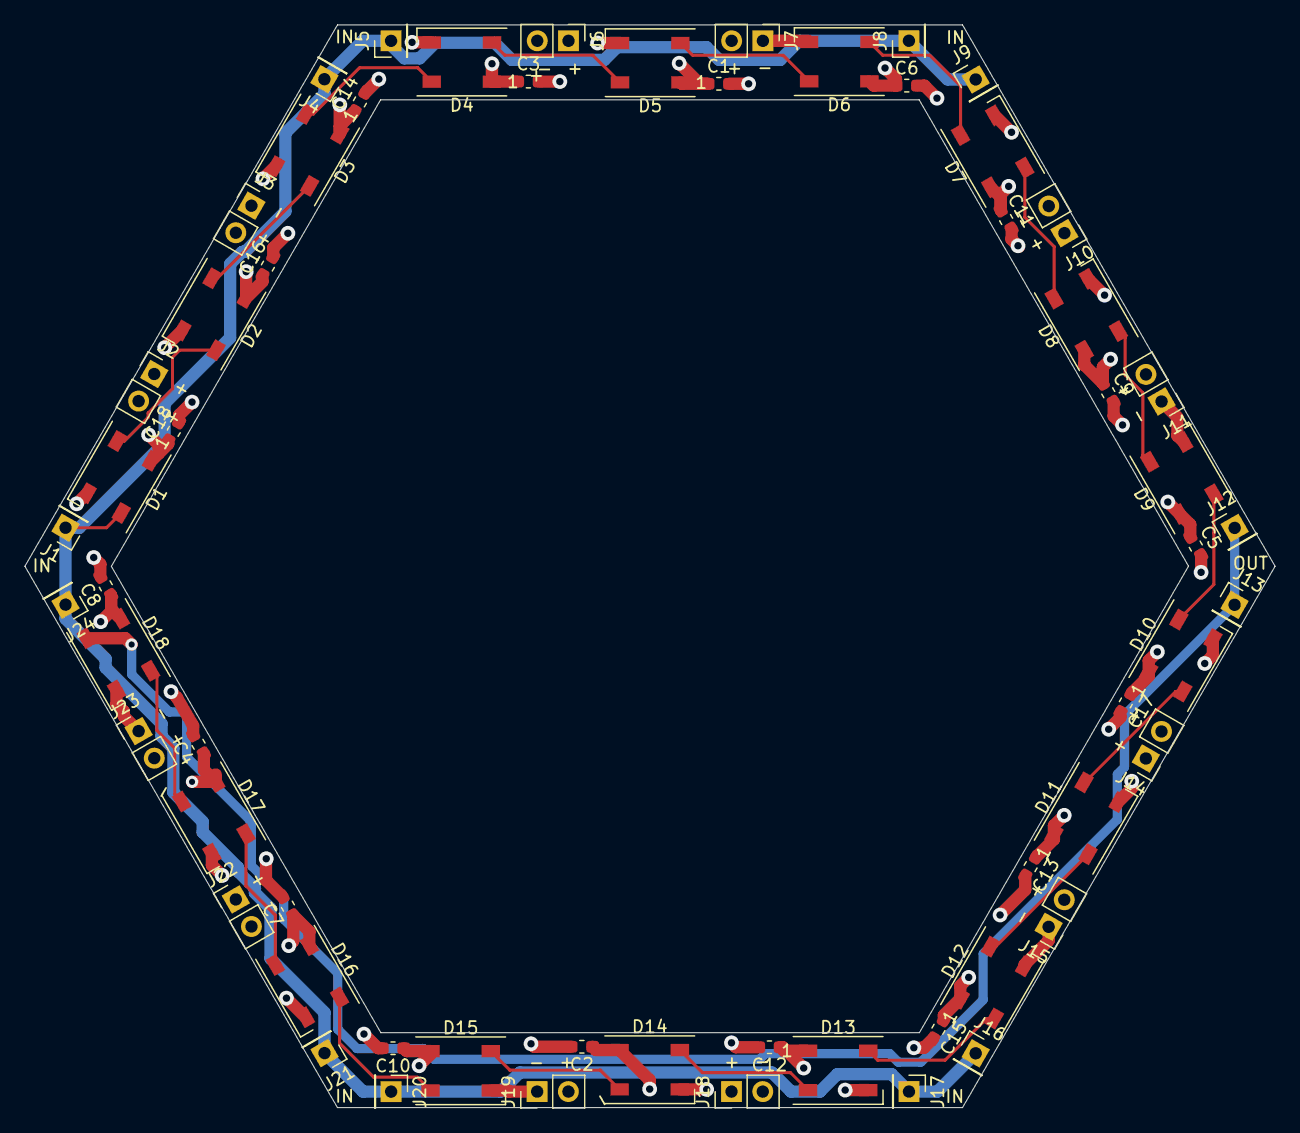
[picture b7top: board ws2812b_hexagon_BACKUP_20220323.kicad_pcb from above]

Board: 4 copper layers, 101.6 x 88.0 mm, 60 parts (0 on the bottom side), 21 nets.

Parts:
C1, C2, C3, C4, C5, C6, C7, C8, C9, C10, C11, C12, C13, C14, C15, C16, C17, C18: C; C_0603_1608Metric_Pad1.05x0.95mm_HandSolder
D1, D2, D3, D4, D5, D6, D7, D8, D9, D10, D11, D12, D13, D14, D15, D16, D17, D18: WS2812B; LED_WS2812B_PLCC4_5.0x5.0mm_P3.2mm
J1, J4, J5, J8, J9, J12, J13, J16, J17, J20, J21, J24: Conn_01x01_Male; PinHeader_1x01_P2.54mm_Vertical
J2, J3, J6, J7, J10, J11, J14, J15, J18, J19, J22, J23: Conn_01x02_Male; PinHeader_1x02_P2.54mm_Vertical

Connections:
+5V: C1.1, C2.1, C3.1, C4.1, C5.1, C6.1, C7.1, C8.1, C9.1, C10.1, C11.1, C12.1, C13.1, C14.1, C15.1, C16.1, C17.1, C18.1, D1.1, D2.1, D3.1, D4.1, D5.1, D6.1, D7.1, D8.1, D9.1, D10.1, D11.1, D12.1, D13.1, D14.1, D15.1, D16.1, D17.1, D18.1, J2.1, J3.2, J6.1, J7.2, J10.1, J11.2, J14.1, J15.2, J18.1, J19.2, J22.1, J23.2
/in: D1.4, J1.1, J4.1, J5.1, J8.1, J9.1, J16.1, J17.1, J20.1, J21.1, J24.1
/int: D10.2, D11.4
/out: D18.2, J12.1, J13.1
GND: C1.2, C2.2, C3.2, C4.2, C5.2, C6.2, C7.2, C8.2, C9.2, C10.2, C11.2, C12.2, C13.2, C14.2, C15.2, C16.2, C17.2, C18.2, D1.3, D2.3, D3.3, D4.3, D5.3, D6.3, D7.3, D8.3, D9.3, D10.3, D11.3, D12.3, D13.3, D14.3, D15.3, D16.3, D17.3, D18.3, J2.2, J3.1, J6.2, J7.1, J10.2, J11.1, J14.2, J15.1, J18.2, J19.1, J22.2, J23.1
unnamed: D1.2, D2.4
unnamed: D2.2, D3.4
unnamed: D3.2, D4.4
unnamed: D4.2, D5.4
unnamed: D5.2, D6.4
unnamed: D6.2, D7.4
unnamed: D7.2, D8.4
unnamed: D8.2, D9.4
unnamed: D9.2, D10.4
unnamed: D11.2, D12.4
unnamed: D12.2, D13.4
unnamed: D13.2, D14.4
unnamed: D14.2, D15.4
unnamed: D15.2, D16.4
unnamed: D16.2, D17.4
unnamed: D17.2, D18.4
